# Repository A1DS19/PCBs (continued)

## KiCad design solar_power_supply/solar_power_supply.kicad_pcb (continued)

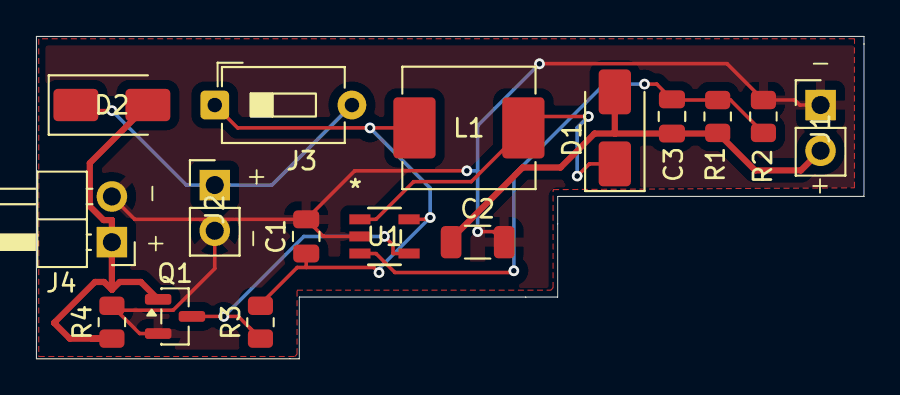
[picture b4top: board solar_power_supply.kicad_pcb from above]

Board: 2 copper layers, 46.0 x 17.9 mm, 16 parts (0 on the bottom side), 8 nets.

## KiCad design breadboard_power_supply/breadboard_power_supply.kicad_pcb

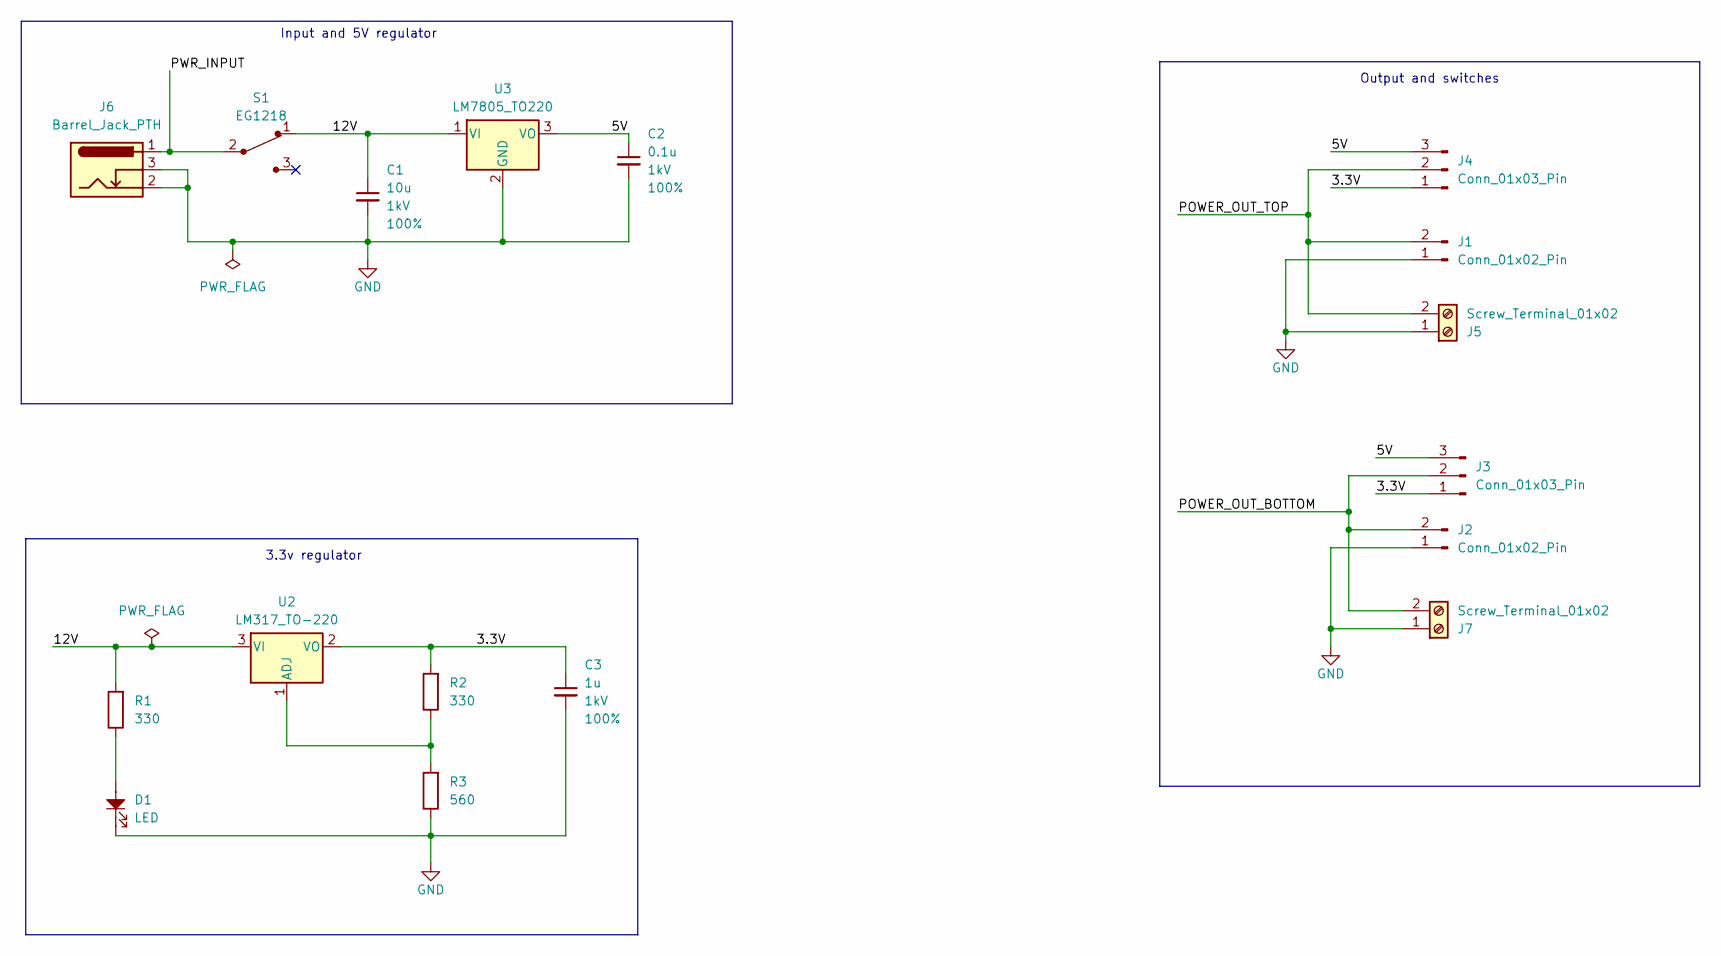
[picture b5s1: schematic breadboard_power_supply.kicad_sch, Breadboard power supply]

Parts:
C1: 10u; C_Disc_D3.0mm_W1.6mm_P2.50mm; Voltage 1kV; Tolerance 100%
C2: 0.1u; C_Disc_D3.0mm_W1.6mm_P2.50mm; Voltage 1kV; Tolerance 100%
C3: 1u; C_Disc_D3.0mm_W1.6mm_P2.50mm; Voltage 1kV; Tolerance 100%
D1: LED; LED_D5.0mm
J1, J2: Conn_01x02_Pin; PinHeader_1x02_P2.54mm_Vertical
J3, J4: Conn_01x03_Pin; PinHeader_1x03_P2.54mm_Vertical
J5, J7: Screw_Terminal_01x02; TerminalBlock_MaiXu_MX126-5.0-02P_1x02_P5.00mm
J6: Barrel_Jack_PTH
R1, R2: 330; R_Axial_DIN0204_L3.6mm_D1.6mm_P7.62mm_Horizontal
R3: 560; R_Axial_DIN0204_L3.6mm_D1.6mm_P7.62mm_Horizontal
S1: EG1218; Switch_Slide_11.6x4mm_EG1218; MPN EG1218; Digi-Key_PN EG1903-ND
U2: LM317_TO-220; TO-220-3_Vertical
U3: LM7805_TO220; TO-220-3_Vertical

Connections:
/3.3V: C3.1, J3.1, J4.1, R2.2, U2.2 (VO)
/5V: C2.1, J3.3, J4.3, U3.3 (VO)
/12V: C1.1, R1.2, S1.1, U2.3 (VI), U3.1 (VI)
/POWER_OUT_BOTTOM: J2.2, J3.2, J7.2
/POWER_OUT_TOP: J1.2, J4.2, J5.2
/PWR_INPUT: J6.1 (PWR), S1.2
GND: C1.2, C2.2, C3.2, D1.1, J1.1, J2.1, J5.1, J6.2 (GND), J6.3 (GNDBREAK), J7.1, R3.1, U3.2 (GND)
unnamed: D1.2, R1.1
unnamed: R2.1, R3.2, U2.1 (ADJ)

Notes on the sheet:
3.3v regulator
Input and 5V regulator
Output and switches

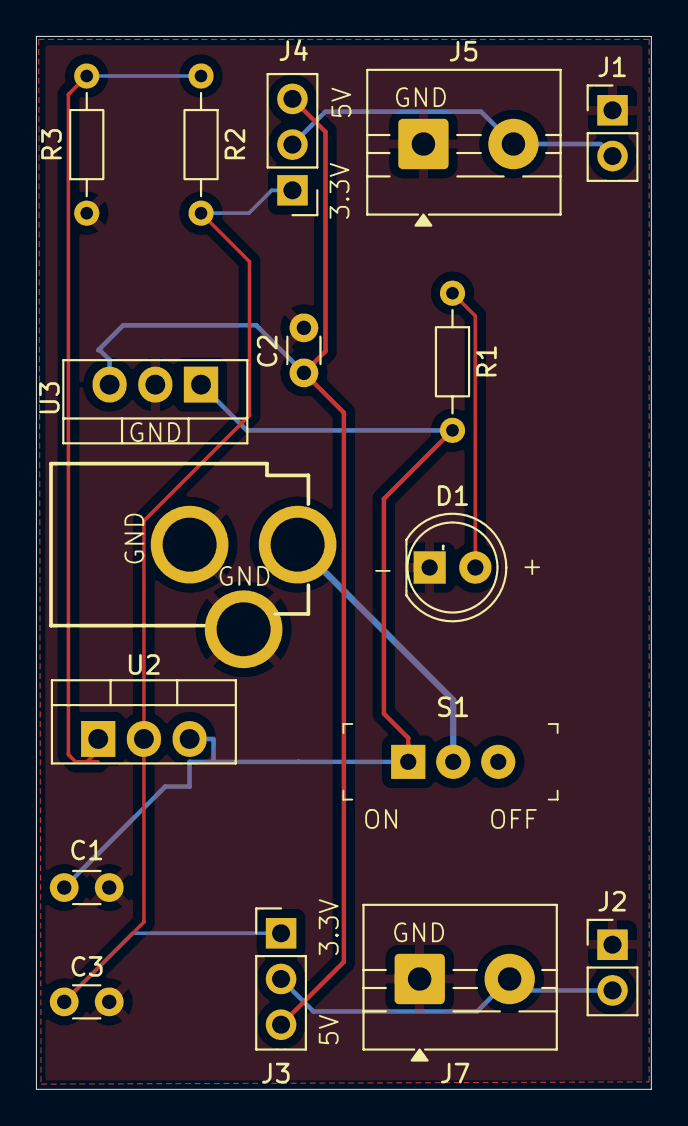
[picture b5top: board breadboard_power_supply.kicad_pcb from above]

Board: 2 copper layers, 34.2 x 58.5 mm, 17 parts (0 on the bottom side), 9 nets.

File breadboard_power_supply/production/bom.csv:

Designator,Footprint,Quantity,Value,LCSC Part #
C1,C_Disc_D3.0mm_W1.6mm_P2.50mm,1,10u,
C2,C_Disc_D3.0mm_W1.6mm_P2.50mm,1,0.1u,
C3,C_Disc_D3.0mm_W1.6mm_P2.50mm,1,1u,
D1,LED_D5.0mm,1,LED,
"J1, J2",PinHeader_1x02_P2.54mm_Vertical,2,Conn_01x02_Pin,
"J3, J4",PinHeader_1x03_P2.54mm_Vertical,2,Conn_01x03_Pin,
"J5, J7",TerminalBlock_MaiXu_MX126-5.0-02P_1x02_P5.00mm,2,Screw_Terminal_01x02,
J6,Barrel_Jack_PTH,1,Barrel_Jack_PTH,
"R1, R2",R_Axial_DIN0204_L3.6mm_D1.6mm_P7.62mm_Horizontal,2,330,
R3,R_Axial_DIN0204_L3.6mm_D1.6mm_P7.62mm_Horizontal,1,560,
S1,Switch_Slide_11.6x4mm_EG1218,1,EG1218,EG1218
U2,TO-220-3_Vertical,1,LM317_TO-220,
U3,TO-220-3_Vertical,1,LM7805_TO220,

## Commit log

2025-11-17 readme
2025-11-21 led torch initial config
2025-11-23 final design LED TORCH
2025-11-23 jlcpcb production files
2025-11-30 breadboard PS
2025-11-30 front and back copper pour
2025-11-30 copper front with fixed DRCC
2025-11-30 breadboard config
2025-11-30 final DRC fixes
2025-11-30 fabrication outputs
2025-11-30 final design DRC fixes
2025-12-01 solar PS
2025-12-01 solar PS copper fills
2025-12-01 final solar PS design
2025-12-01 init mcu datalogger
2025-12-01 symbols and libraries for mcu
2025-12-01 added values to symbols
2025-12-01 footprints
2025-12-01 connect labels between sheets
2025-12-01 net classes
2025-12-01 comment schematic
2025-12-03 2 layer pcb with routing
2025-12-03 back copper
2025-12-03 back copper and final 2 layer connections
2025-12-03 back silkscreen details
2025-12-03 back copper vias
2025-12-03 silkscreen
2025-12-03 FIX PINS
2025-12-03 fix design error
2025-12-03 bom, cpl, drill files
2025-12-21 datalogger
2025-12-21 add graphics to mcu
2025-12-21 html BOM
2025-12-23 logos
2025-12-23 logos corrected
2025-12-23 esp32 iot manager init
2025-12-23 Created symbols, footprints, configs Voltage regulator Next esp32 section, memory, sd card
2025-12-24 esp32 page and datasheets
2025-12-24 finished esp32 sheet, next sensors
2025-12-24 sensor and user interface done
2025-12-25 corrected erc errors
2025-12-26 finished design of pcb, next copper zones, routing
2025-12-28 4 layer pcb design done
2026-01-11 esp32 manager layout
2026-01-11 copper zones 1
2026-01-11 copper zones
2026-01-15 added 3.3v testpoint, routed diff pairs
2026-01-15 routed power, gnd lines
2026-01-15 signal routing 1 error
2026-01-15 finish routinh
2026-01-15 FIX DRC
2026-01-18 3d models
2026-01-20 production build for manufacturing
2026-01-20 flip transistor
2026-01-21 finish esp32
